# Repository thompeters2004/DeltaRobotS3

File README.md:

# DeltaRobotS3
This is the GitHub for the Delta Robot S3 project of Thom and Ruben.

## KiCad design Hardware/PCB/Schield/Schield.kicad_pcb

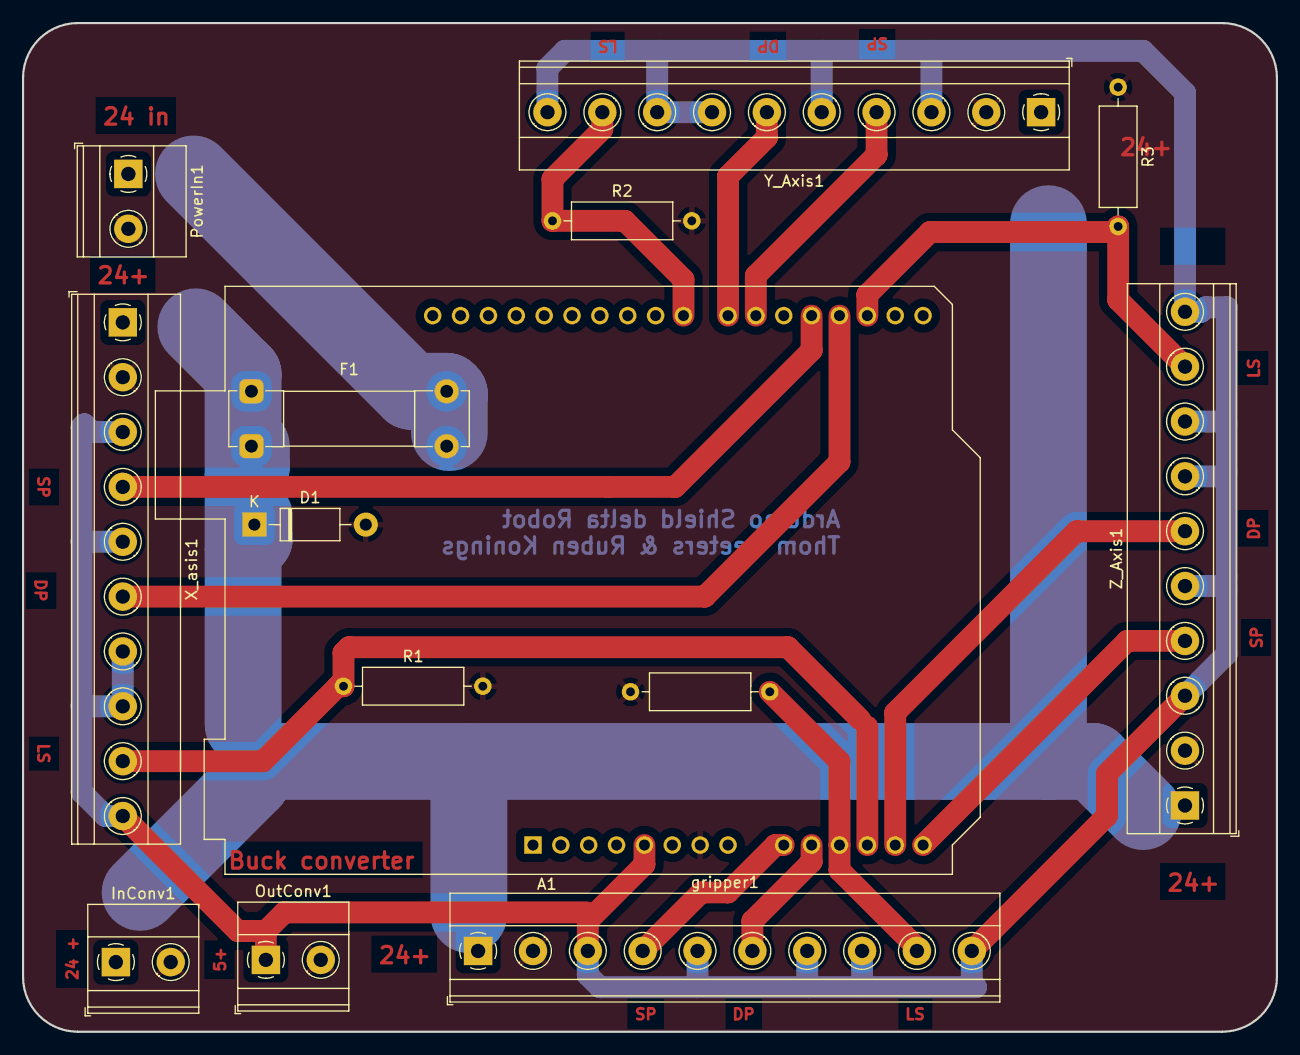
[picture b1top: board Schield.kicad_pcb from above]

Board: 2 copper layers, 114.3 x 91.9 mm, 14 parts (0 on the bottom side), 16 nets.

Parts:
A1: Arduino_UNO_R3
D1: 1N47xxA; D_DO-41_SOD81_P10.16mm_Horizontal
F1: Fuse; Fuseholder_Clip-5x20mm_Bel_FC-203-22_Lateral_P17.80x5.00mm_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
InConv1: Screw_Terminal_01x02; TerminalBlock_Phoenix_MKDS-1,5-2_1x02_P5.00mm_Horizontal
OutConv1: Screw_Terminal_01x02; TerminalBlock_Phoenix_MKDS-1,5-2_1x02_P5.00mm_Horizontal
PowerIn1: Screw_Terminal_01x02; TerminalBlock_Phoenix_MKDS-1,5-2_1x02_P5.00mm_Horizontal
R1, R2, R3, R4: 1KR; R_Axial_DIN0309_L9.0mm_D3.2mm_P12.70mm_Horizontal
X_asis1: Screw_Terminal_01x10; TerminalBlock_Phoenix_MKDS-1,5-10_1x10_P5.00mm_Horizontal
Y_Axis1: Screw_Terminal_01x10; TerminalBlock_Phoenix_MKDS-1,5-10_1x10_P5.00mm_Horizontal
Z_Axis1: Screw_Terminal_01x10; TerminalBlock_Phoenix_MKDS-1,5-10_1x10_P5.00mm_Horizontal
gripper1: Screw_Terminal_01x10; TerminalBlock_Phoenix_MKDS-1,5-10_1x10_P5.00mm_Horizontal

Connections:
/5V: A1.5 (+5V), OutConv1.1, X_asis1.3, X_asis1.5, X_asis1.7, X_asis1.8, X_asis1.10, Y_Axis1.3, Y_Axis1.5, Y_Axis1.7, Y_Axis1.8, Y_Axis1.10, Z_Axis1.3, Z_Axis1.5, Z_Axis1.7, Z_Axis1.8, Z_Axis1.10, gripper1.3, gripper1.5, gripper1.7, gripper1.8, gripper1.10
/24 V in: F1.2, PowerIn1.1
/24+: D1.1 (K), F1.1, InConv1.1, X_asis1.1, Y_Axis1.1, Z_Axis1.1, gripper1.1
/DirGrip: A1.10 (A1), gripper1.6
/DirX: A1.18 (D3), X_asis1.6
/DirY: A1.22 (D7), Y_Axis1.6
/DirZ: A1.13 (SDA/A4), Z_Axis1.6
/LimitSwGrip: A1.11 (A2), R4.2, gripper1.9
/LimitSwX: A1.12 (A3), R1.1, X_asis1.9
/LimitSwY: A1.23 (D8), R2.1, Y_Axis1.9
/LimitSwZ: A1.17 (D2), R3.2, Z_Axis1.9
/StepGrip: A1.9 (A0), gripper1.4
/StepX: A1.19 (D4), X_asis1.4
/StepY: A1.21 (D6), Y_Axis1.4
/stepZ: A1.14 (SCL/A5), Z_Axis1.4
GND: A1.7 (GND), D1.2 (A), InConv1.2, OutConv1.2, PowerIn1.2, R1.2, R2.2, R3.1, R4.1, X_asis1.2, Y_Axis1.2, Z_Axis1.2, gripper1.2
